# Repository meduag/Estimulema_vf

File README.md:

# Estimulema_vf
Hola como estás!!

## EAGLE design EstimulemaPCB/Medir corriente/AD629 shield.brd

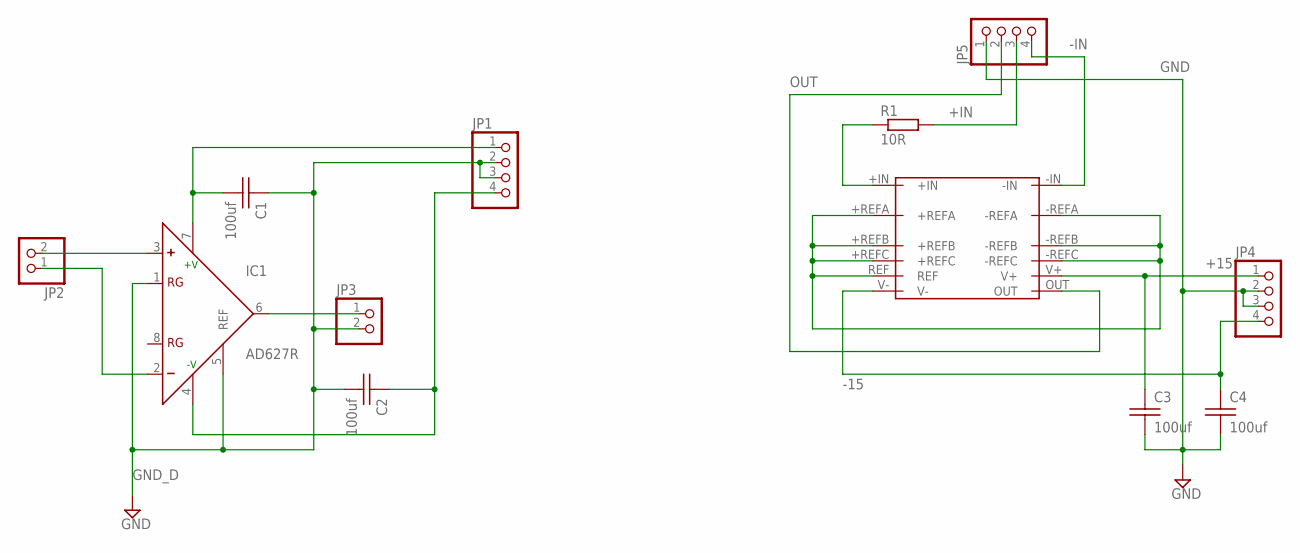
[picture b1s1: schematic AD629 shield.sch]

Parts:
C1, C2, C3, C4: 100uf; CAP_CER_SMD-0805
IC1: AD627R; SO8
JP1, JP4, JP5: PINHD-1X4; 1X04
JP2, JP3: PINHD-1X2; 1X02
R1: 10R; RESISTENCIA_0805
U$1: LT6375; LT6375_MS16(12)

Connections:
+15: C3.1, JP4.1, U$1.V+
+IN: JP5.3, R1.2
-15: C4.1, JP4.4, U$1.V-
-IN: JP5.4, U$1.-IN
GND: C3.2, C4.2, JP4.2, JP4.3, JP5.1
GND_D: C1.1, C2.2, IC1.1 (RG), IC1.5 (REF), JP1.2, JP1.3, JP3.2
unnamed: IC1.3 (+), JP2.2
unnamed: IC1.2 (-), JP2.1
unnamed: C1.2, IC1.7 (+V), JP1.1
unnamed: C2.1, IC1.4 (-V), JP1.4
unnamed: IC1.6 (OUT), JP3.1
unnamed: U$1.+REFA, U$1.+REFB, U$1.+REFC, U$1.-REFA, U$1.-REFB, U$1.-REFC, U$1.REF
unnamed: R1.1, U$1.+IN
OUT: JP5.2, U$1.OUT

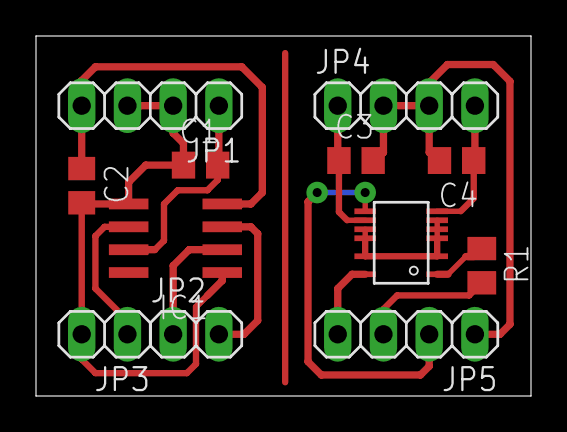
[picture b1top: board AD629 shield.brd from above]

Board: 2 copper layers, 27.5 x 20.0 mm, 12 parts (0 on the bottom side), 14 nets.
